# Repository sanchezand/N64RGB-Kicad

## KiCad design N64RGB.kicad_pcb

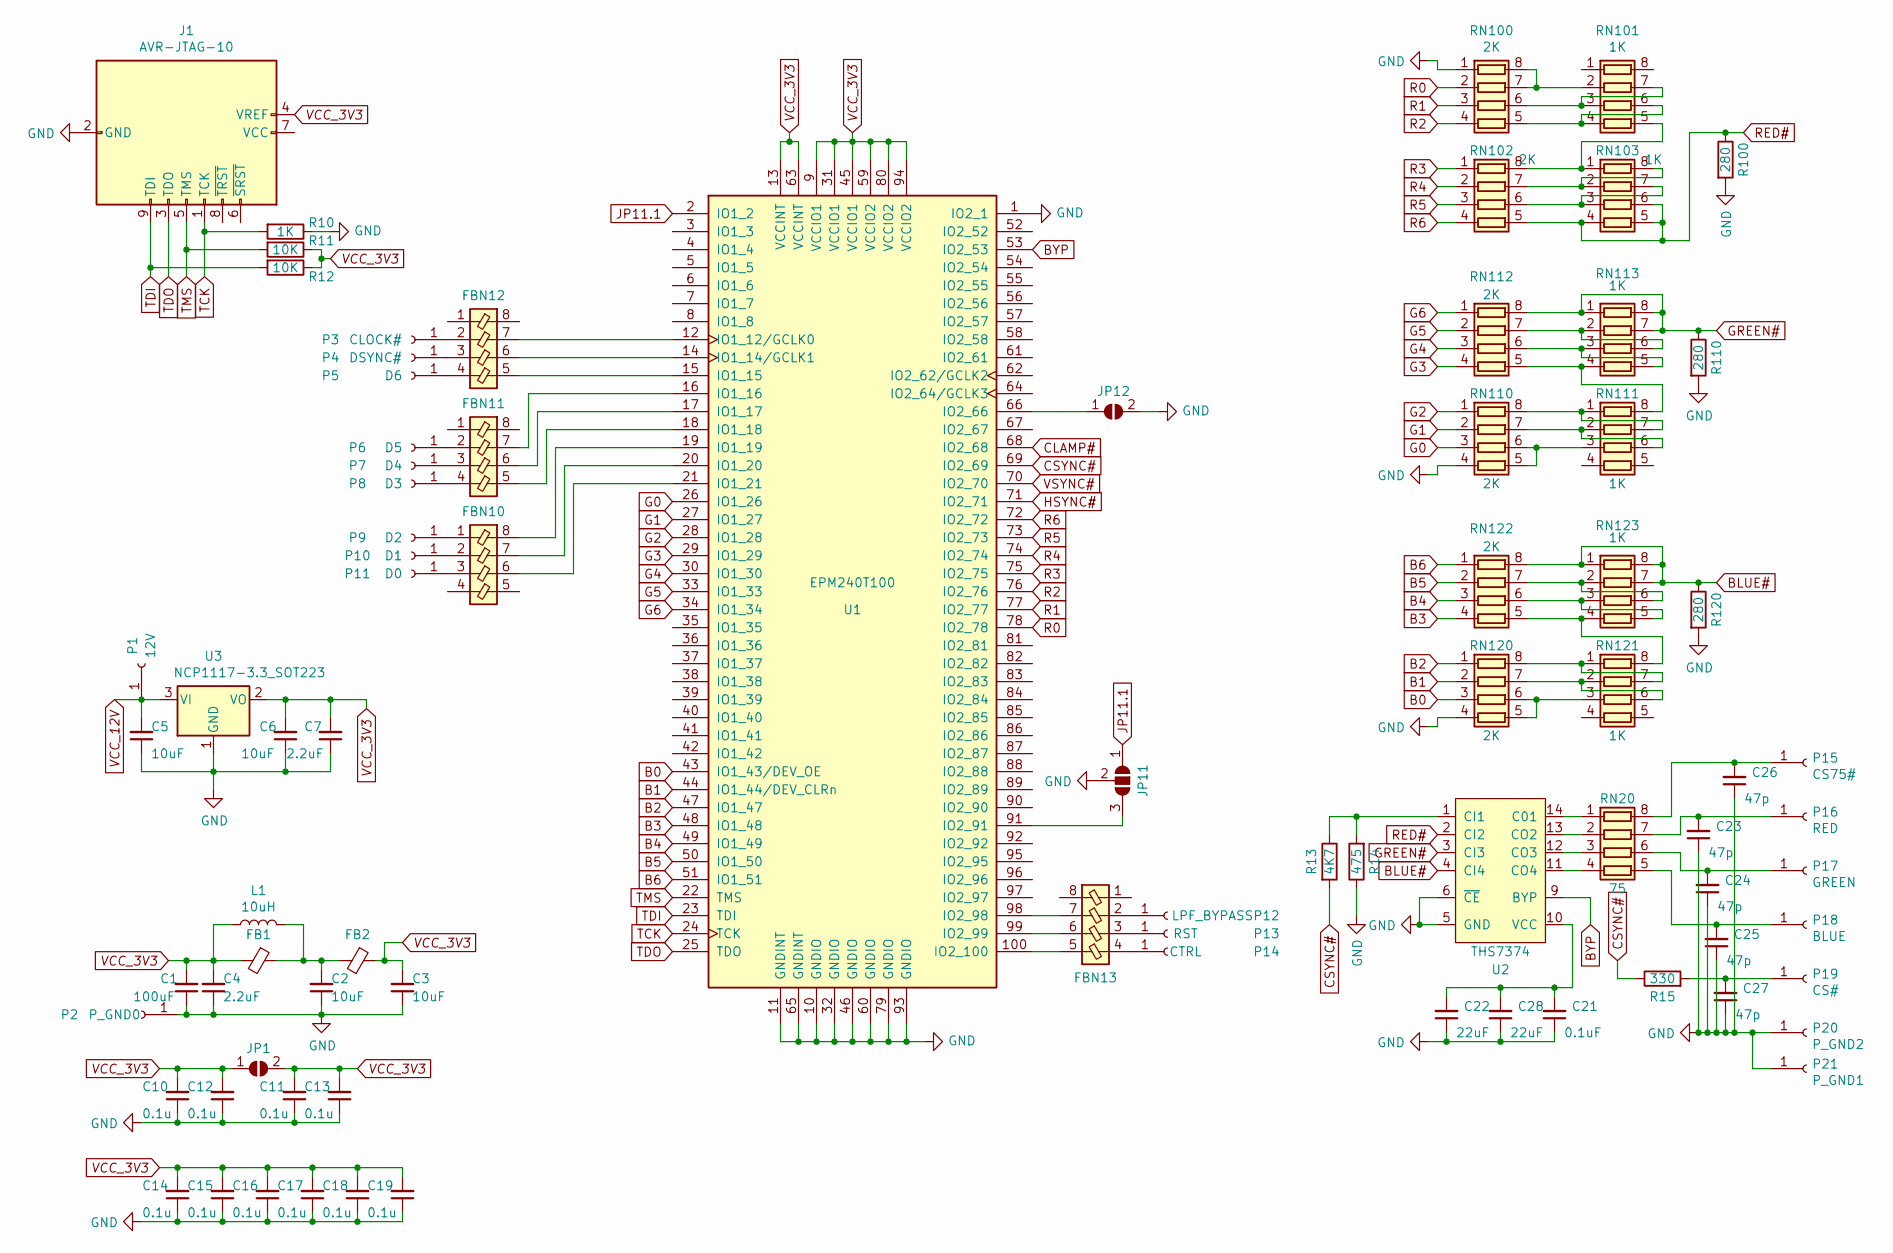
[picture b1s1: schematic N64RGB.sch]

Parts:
C1: 100uF; C_0805_2012Metric_Pad1.15x1.40mm_HandSolder
C2, C3, C5, C6: 10uF; C_0805_2012Metric_Pad1.15x1.40mm_HandSolder
C4, C7: 2.2uF; C_0805_2012Metric_Pad1.15x1.40mm_HandSolder
C10, C11, C12, C13, C14, C15, C16, C17, C18, C19: 0.1u; C_0805_2012Metric_Pad1.15x1.40mm_HandSolder
C21: 0.1uF; C_0805_2012Metric_Pad1.15x1.40mm_HandSolder
C22, C28: 22uF; C_0805_2012Metric_Pad1.15x1.40mm_HandSolder
C23, C24, C25, C26, C27: 47p; C_0805_2012Metric_Pad1.15x1.40mm_HandSolder
FB1, FB2: Ferrite_Bead_Small; R_0805_2012Metric_Pad1.15x1.40mm_HandSolder
FBN10, FBN11, FBN12, FBN13: Ferrite_Bead_Pack04; R_Array_Convex_4x1206
J1: AVR-JTAG-10; PinHeader_2x05_P2.54mm_Vertical
JP1, JP12: SolderJumper_2_Open; SolderJumper-2_P1.3mm_Open_RoundedPad1.0x1.5mm
JP11: SolderJumper_3_Open; SolderJumper-3_P1.3mm_Open_RoundedPad1.0x1.5mm_NumberLabels
L1: 10uH; L_0805_2012Metric_Pad1.15x1.40mm_HandSolder
P1: 12V; TestPoint_Pad_2.5x2.5mm
P2: P_GND0; TestPoint_Pad_2.5x2.5mm
P3: CLOCK#; TestPoint_Pad_2.5x2.5mm
P4: DSYNC#; TestPoint_Pad_2.5x2.5mm
P5: D6; TestPoint_Pad_2.5x2.5mm
P6: D5; TestPoint_Pad_2.5x2.5mm
P7: D4; TestPoint_Pad_2.5x2.5mm
P8: D3; TestPoint_Pad_2.5x2.5mm
P9: D2; TestPoint_Pad_2.5x2.5mm
P10: D1; TestPoint_Pad_2.5x2.5mm
P11: D0; TestPoint_Pad_2.5x2.5mm
P12: LPF_BYPASS; TestPoint_Pad_2.5x2.5mm
P13: RST; TestPoint_Pad_2.5x2.5mm
P14: CTRL; TestPoint_Pad_2.5x2.5mm
P15: CS75#; TestPoint_Pad_2.5x2.5mm
P16: RED; TestPoint_Pad_2.5x2.5mm
P17: GREEN; TestPoint_Pad_2.5x2.5mm
P18: BLUE; TestPoint_Pad_2.5x2.5mm
P19: CS#; TestPoint_Pad_2.5x2.5mm
P20: P_GND2; TestPoint_Pad_2.5x2.5mm
P21: P_GND1; TestPoint_Pad_2.5x2.5mm
R10: 1K; R_0805_2012Metric_Pad1.15x1.40mm_HandSolder
R11, R12: 10K; R_0805_2012Metric_Pad1.15x1.40mm_HandSolder
R13: 4K7; R_0805_2012Metric_Pad1.15x1.40mm_HandSolder
R14: 475; R_0805_2012Metric_Pad1.15x1.40mm_HandSolder
R15: 330; R_0805_2012Metric_Pad1.15x1.40mm_HandSolder
R100, R110, R120: 280; R_0805_2012Metric_Pad1.15x1.40mm_HandSolder
RN20: 75; R_Array_Convex_4x1206
RN100, RN102, RN110, RN112, RN120, RN122: 2K; R_Array_Convex_4x1206
RN101, RN103, RN111, RN113, RN121, RN123: 1K; R_Array_Convex_4x1206
U1: EPM240T100; LQFP-100_14x14mm_P0.5mm
U2: THS7374; TSSOP-14_4.4x5mm_P0.65mm
U3: NCP1117-3.3_SOT223; SOT-223-3_TabPin2

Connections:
B0: RN120.3 (R3.1), U1.43 (IO1_43/DEV_OE)
B1: RN120.2 (R2.1), U1.44 (IO1_44/DEV_CLRn)
B2: RN120.1 (R1.1), U1.47 (IO1_47)
B3: RN122.4 (R4.1), U1.48 (IO1_48)
B4: RN122.3 (R3.1), U1.49 (IO1_49)
B5: RN122.2 (R2.1), U1.50 (IO1_50)
B6: RN122.1 (R1.1), U1.51 (IO1_51)
BLUE#: R120.1, RN122.8 (R1.2), RN123.1 (R1.1), RN123.7 (R2.2), RN123.8 (R1.2), U2.4 (CI4)
BYP: U1.53 (IO2_53), U2.9 (BYP)
CLAMP#: U1.68 (IO2_68)
CSYNC#: R13.2, R15.1, U1.69 (IO2_69)
G0: RN110.3 (R3.1), U1.26 (IO1_26)
G1: RN110.2 (R2.1), U1.27 (IO1_27)
G2: RN110.1 (R1.1), U1.28 (IO1_28)
G3: RN112.4 (R4.1), U1.29 (IO1_29)
G4: RN112.3 (R3.1), U1.30 (IO1_30)
G5: RN112.2 (R2.1), U1.33 (IO1_33)
G6: RN112.1 (R1.1), U1.34 (IO1_34)
GND: C1.1, C2.1, C3.1, C4.1, C5.1, C6.1, C7.1, C10.1, C11.1, C12.1, C13.1, C14.1, C15.1, C16.1, C17.1, C18.1, C19.1, C21.1, C22.1, C23.1, C24.1, C25.1, C26.1, C27.1, C28.1, J1.2 (GND), J1.10 (GND), JP11.2 (C), JP12.2 (B), P2.1, P20.1, P21.1, R10.1, R14.1, R100.2, R110.2, R120.2, RN100.1 (R1.1), RN110.4 (R4.1), RN120.4 (R4.1), U1.1 (IO2_1), U1.10 (GNDIO), U1.11 (GNDINT), U1.32 (GNDIO), U1.46 (GNDIO), U1.60 (GNDIO), U1.65 (GNDINT), U1.79 (GNDIO), U1.93 (GNDIO), U2.5 (GND), U2.6 (~CE), U3.1 (GND)
GREEN#: R110.1, RN112.8 (R1.2), RN113.1 (R1.1), RN113.7 (R2.2), RN113.8 (R1.2), U2.3 (CI3)
HSYNC#: U1.71 (IO2_71)
JP11.1: JP11.1 (A), U1.2 (IO1_2)
unnamed: C2.2, FB1.1, FB2.2, L1.2
unnamed: C21.2, C22.2, C28.2, U2.10 (VCC)
unnamed: C23.2, P16.1, RN20.7 (R2.2)
unnamed: C24.2, P17.1, RN20.6 (R3.2)
unnamed: C25.2, P18.1, RN20.5 (R4.2)
unnamed: C26.2, P15.1, RN20.8 (R1.2)
unnamed: C27.2, P19.1, R15.2
unnamed: FBN10.1, P9.1
unnamed: FBN10.2, P10.1
unnamed: FBN10.3, P11.1
unnamed: FBN10.6, U1.21 (IO1_21)
unnamed: FBN10.7, U1.20 (IO1_20)
unnamed: FBN10.8, U1.19 (IO1_19)
unnamed: FBN11.2, P6.1
unnamed: FBN11.3, P7.1
unnamed: FBN11.4, P8.1
unnamed: FBN11.5, U1.18 (IO1_18)
unnamed: FBN11.6, U1.17 (IO1_17)
unnamed: FBN11.7, U1.16 (IO1_16)
unnamed: FBN12.2, P3.1
unnamed: FBN12.3, P4.1
unnamed: FBN12.4, P5.1
unnamed: FBN12.5, U1.15 (IO1_15)
unnamed: FBN12.6, U1.14 (IO1_14/GCLK1)
unnamed: FBN12.7, U1.12 (IO1_12/GCLK0)
unnamed: FBN13.2, P12.1
unnamed: FBN13.3, P13.1
unnamed: FBN13.4, P14.1
unnamed: FBN13.5, U1.100 (IO2_100)
unnamed: FBN13.6, U1.99 (IO2_99)
unnamed: FBN13.7, U1.98 (IO2_98)
unnamed: JP11.3 (B), U1.91 (IO2_91)
unnamed: JP12.1 (A), U1.66 (IO2_66)
unnamed: R13.1, R14.2, U2.1 (CI1)
unnamed: RN20.1 (R1.1), U2.14 (C01)
unnamed: RN20.2 (R2.1), U2.13 (CO2)
unnamed: RN20.3 (R3.1), U2.12 (CO3)
unnamed: RN20.4 (R4.1), U2.11 (CO4)
unnamed: RN100.5 (R4.2), RN101.4 (R4.1), RN101.6 (R3.2)
unnamed: RN100.6 (R3.2), RN101.3 (R3.1), RN101.7 (R2.2)
unnamed: RN100.7 (R2.2), RN100.8 (R1.2), RN101.2 (R2.1)
unnamed: RN101.5 (R4.2), RN102.8 (R1.2), RN103.1 (R1.1)
unnamed: RN102.6 (R3.2), RN103.3 (R3.1), RN103.7 (R2.2)
unnamed: RN102.7 (R2.2), RN103.2 (R2.1), RN103.8 (R1.2)
unnamed: RN110.5 (R4.2), RN110.6 (R3.2), RN111.3 (R3.1)
unnamed: RN110.7 (R2.2), RN111.2 (R2.1), RN111.6 (R3.2)
unnamed: RN110.8 (R1.2), RN111.1 (R1.1), RN111.7 (R2.2)
unnamed: RN111.8 (R1.2), RN112.5 (R4.2), RN113.4 (R4.1)
unnamed: RN112.6 (R3.2), RN113.3 (R3.1), RN113.5 (R4.2)
unnamed: RN112.7 (R2.2), RN113.2 (R2.1), RN113.6 (R3.2)
unnamed: RN120.5 (R4.2), RN120.6 (R3.2), RN121.3 (R3.1)
unnamed: RN120.7 (R2.2), RN121.2 (R2.1), RN121.6 (R3.2)
unnamed: RN120.8 (R1.2), RN121.1 (R1.1), RN121.7 (R2.2)
unnamed: RN121.8 (R1.2), RN122.5 (R4.2), RN123.4 (R4.1)
unnamed: RN122.6 (R3.2), RN123.3 (R3.1), RN123.5 (R4.2)
unnamed: RN122.7 (R2.2), RN123.2 (R2.1), RN123.6 (R3.2)
R0: RN100.2 (R2.1), U1.78 (IO2_78)
R1: RN100.3 (R3.1), U1.77 (IO2_77)
R2: RN100.4 (R4.1), U1.76 (IO2_76)
R3: RN102.1 (R1.1), U1.75 (IO2_75)
R4: RN102.2 (R2.1), U1.74 (IO2_74)
R5: RN102.3 (R3.1), U1.73 (IO2_73)
R6: RN102.4 (R4.1), U1.72 (IO2_72)
RED#: R100.1, RN102.5 (R4.2), RN103.4 (R4.1), RN103.5 (R4.2), RN103.6 (R3.2), U2.2 (CI2)
TCK: J1.1 (TCK), R10.2, U1.24 (TCK)
TDI: J1.9 (TDI), R12.2, U1.23 (TDI)
TDO: J1.3 (TDO), U1.25 (TDO)
TMS: J1.5 (TMS), R11.2, U1.22 (TMS)
VCC_3V3: C1.2, C3.2, C4.2, C6.2, C7.2, C10.2, C11.2, C12.2, C13.2, C14.2, C15.2, C16.2, C17.2, C18.2, C19.2, FB1.2, FB2.1, J1.4 (VREF), JP1.1 (A), JP1.2 (B), L1.1, R11.1, R12.1, U1.9 (VCCIO1), U1.13 (VCCINT), U1.31 (VCCIO1), U1.45 (VCCIO1), U1.59 (VCCIO2), U1.63 (VCCINT), U1.80 (VCCIO2), U1.94 (VCCIO2), U3.2 (VO)
VCC_12V: C5.2, P1.1, U3.3 (VI)
VSYNC#: U1.70 (IO2_70)

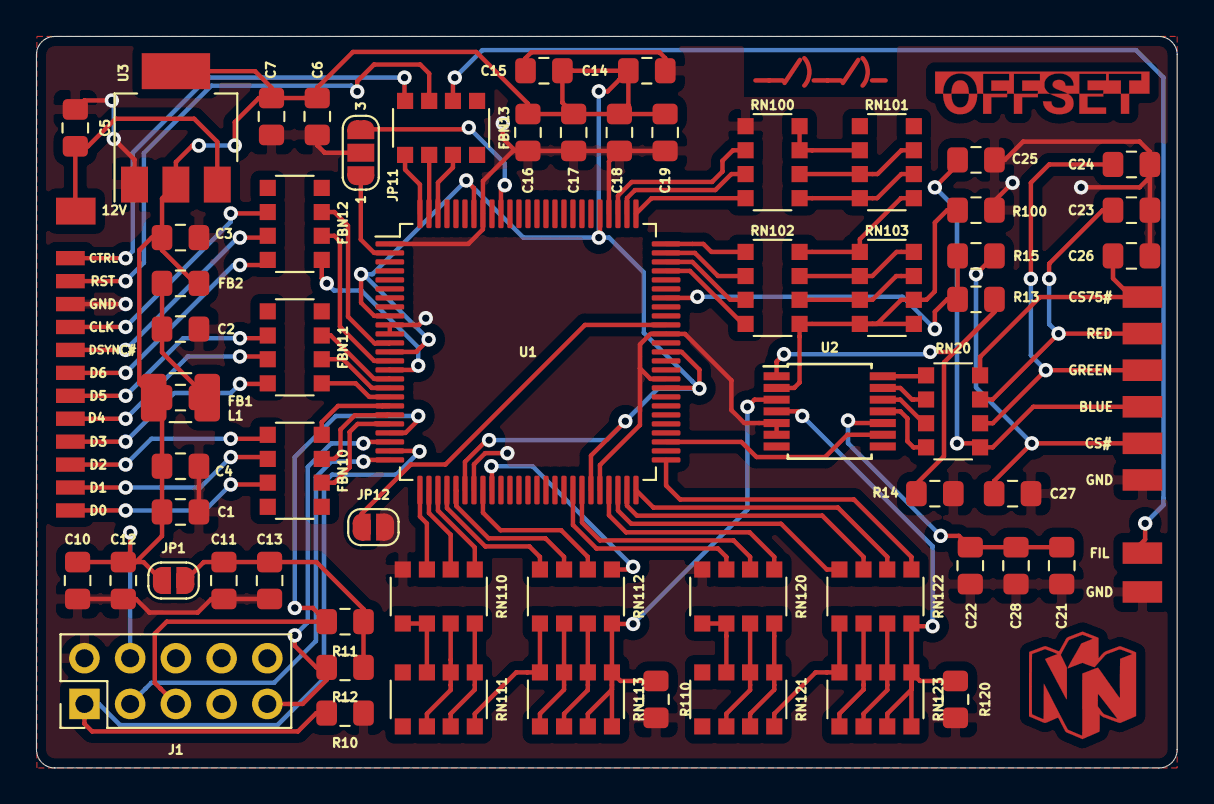
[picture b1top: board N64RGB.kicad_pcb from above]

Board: 2 copper layers, 63.4 x 40.6 mm, 82 parts (0 on the bottom side), 90 nets.

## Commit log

2020-05-19 Initial commit, finished PCB and schematic
